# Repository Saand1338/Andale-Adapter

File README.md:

# Andale Adapter

The Andale Adapter Project is a Wii Remote–sized adapter for Wii Guitar Hero Controllers, powered by a Raspberry Pi Pico/Pico W running Santroller firmware.
This project, through the Santroller firmware, enables these controllers to function on PC/Xbox/PlayStation platforms through USB connectivity, or though Bluetooth via custom recievers also powered by a Raspberry Pi Pico W running Santroller firmware.
The circuit boards have been designed with hand assembly in mind, and requires the soldering of both through-hole components and surface mount devices (SMD). The use of SMD components makes a soldering plate recommended equipment, but sufficient pad clearence has been used to enable careful hand soldering.

---

## Repository Structure

This repository contains three main sections:

1. **Andale Adapter** - the Adapter itself, the "brains" of the project.
2. **Slim Receiver** - a compact Bluetooth receiver, designed for low height.
3. **Tiny Receiver** - a minimal volume Bluetooth receiver, designed for portability.

All three sections include:
- KiCAD project files and Gerber outputs.
- STL files for 3D printed enclosures.
- Autodesk Fusion project files for the STLs.
- Bills of Material (BOM) files in CSV format.

> **Note:** All enclosure STLs are designed for resin printing. Extensive use of overhangs makes them less ideal for FDM printing.

---

## Overview

The Andale Adapter is designed with certain optional elements. Depending on the desired configuration, builders can choose to integrate multiple additional features:

 Feature | Description |
----------|--------------|
 Bluetooth and/or USB connectivity | Supports both wireless and wired operation. |
 RGB LED support | Allows support for up to 10 RGB LEDs on customised PCBs though a USB Micro port. |
 Controller authentication support | Required for consoles that need controller verification, done so over a regular USB port. |
 AA battery power | Recommended for Bluetooth operation. Designed around NiMH rechargable batteries. |

> **Note:** For a Bluetooth setup USB Auth is not required on the adapter. It's only required for wired configuration on console systems that require it.

---

## Assembly Order

Due to the mixed component types and modular structure, the following rough build order is recommended:

1. Prepare customised components (e.g., modified headers, trimmed USB connectors).
2. Solder Surface Mount Devices (SMDs).
3. Solder USB connectors (if applicable).
4. Solder through-hole components (e.g., headers, battery terminals).
5. Solder add-in boards (Pico, Nunchuck adapter, accelerometer).
6. Final assembly into enclosures.

---

## Andale Adapter

The Andale Adapter is the primary focus of the project, and contains the most complex components.
A small internal cable can be made to route the Pico USB Micro to a USB-C breakout board, and a sample wiring diagram is included.
Due to height & space limitations, the PCBs in the adapter are 1mm thick by design.

### Adapter Components

| Component | Purpose |
|------------|----------|
| Mainboard | Core PCB carrying the Pico, accelerometer, and Nunchuck adapter. |
| Battery Board | Optional PCB for AA NiMH battery power and On/Off switch. |
| Connector Board | Optional PCB for controller authentication, RGB integration (with voltage boost). |
| Internal Cable | Adapting and routing the Pico USB Micro Port to a USB-C Port on the top of the case |

### Build Notes
- For Bluetooth setups, a Raspberry Pi Pico W is a requirement.
- For USB setups, either Pico or Pico W may be used.
- A USB cable or the USB-C breakout may be hardwired to the mainboard if preferred over using an internal USB Micro cable.

---

### Bill of Materials - Mainboard

| Part | Component Type | Part Code | Qty | Purpose | Notes |
|------|----------------|------------|------|----------|-------|
| Pi Pico W | Commercial Product | - | 1 | Controller logic | Use Pico for wired-only builds. |
| 1x10 Low Profile Male Header | Through-hole | - | 2 | Mount for Pico W | - |
| 1x05 Male Header | Through-hole | - | 1 | Mount for Nunchuck Adapter | Requires double insulator height. |
| Adafruit Nunchuck Adapter | Commercial Product | - | 1 | Nunchuck connector integration | - |
| 1x08 Low Profile Male Header | Through-hole | - | 1 | Mount for ADXL345 | - |
| Triple Axis SEN0032 ADXL345 Board | Commercial Product | - | 1 | Accelerometer | Other ADXL345 board compatibility is uncertain. |
| 1x02 Low Profile Female Header | Through-hole | - | 1 | Powerboard plug | - |
| 1x04 Low Profile Female Header | Through-hole | - | 2 | Connector board plug | Insulator height 4 or 7 mm. |
| 20V 1A Schottky Diode | SMD (SOT-123F) | MBR120VLSFT1G | 1 | Power direction regulator | Required for battery or hardwired power. |
| LED | SMD (1208) | QBLP653-S5 | 1 | Low-voltage indicator | - |
| 1.25 V Voltage Shunt | SMD (DBZ) | TLV431DBZ | 1 | Voltage detection | Must use TL**V**431 variant. |
| 3.57 kΩ Resistor | SMD (0805) | RQ73C2A3K57BTD | 1 | Voltage divider | - |
| 2.74 kΩ Resistor | SMD (0805) | RQ73C2A2K74BTD | 1 | Voltage divider | - |
| 221 Ω Resistor | SMD (0805) | RQ73C2A221RBTD | 1 | LED current limiter | Value not optimal but functional. |
| USB Male to Micro Adapter | Commercial Product | - | 1 | Internal cable | Optional; unnecessary for a directly hardwired setup. |
| Adafruit USB-C Downstream Breakout | Commercial Product | - | 1 | External connector | - |
| Silicone Ribbon Cable (4× 28 AWG) | Commercial Product | - | 1 | Internal wiring | - |

---

### Bill of Materials - Battery Board

| Part | Component Type | Part Code | Qty | Purpose | Notes |
|------|----------------|------------|------|----------|-------|
| 1x2 Male Header | Through-hole | - | 1 | Plug to mainboard | Mount upside down if using 7 mm tall header sockets. |
| On-Off Switch | Through-hole | AS11AH | 1 | Power control | - |
| AA Battery Terminal, Plate | Through-hole | Keystone 595 | 2 | Battery contact | - |
| AA Battery Terminal, Coil | Through-hole | Keystone 628 | 2 | Battery contact | - |

---

### Bill of Materials - Connector Board

| Part | Component Type | Part Code | Qty | Purpose | Notes |
|------|----------------|------------|------|----------|-------|
| 1x04 Male Header | Through-hole | - | 2 | Plug to mainboard | Mount upside down if using 7 mm tall header sockets. |
| 1x04 Low Profile Male Header | Through-hole | - | 1 | Mount for TinyBoost | - |
| USB Micro Female | Through-hole | Amphenol 10118194-0001LF | 1 | RGB integration | Nonstandard use of USB port. |
| USB A Female | Through-hole | GCT USB1046 | 1 | Controller auth | Required for wired console use. |
| Adafruit MiniBoost 5V | Commercial Product | - | 1 | Voltage boost for RGB | Skip for non-battery builds. |

---

## Slim Receiver

The Slim Receiver is a Bluetooth receiver designed for consoles or PCs.
It uses a Pico W, connects directly via USB-A, and includes a secondary port for controller auth.

### Key Characteristics
- Compact vertical height.
- Left- or right-offset USB configuration so two recievers can be used side-by-side

### Bill of Materials - Slim Receiver

| Part | Component Type | Part Code | Qty | Purpose | Notes |
|------|----------------|------------|------|----------|-------|
| Pi Pico W | Commercial Product | - | 1 | Logic | Required. |
| 1x10 Low Profile Male Header | Through-hole | - | 2 | Mount for Pico W | - |
| USB A Male | Through-hole | CNCTech 1001-011-01101 | 1 | Plug for console/PC | Offset configuration possible. |
| USB A Female | Through-hole | GCT USB1046 | 1 | Auth plug | Required for consoles needing authentication. |
| 3.18 mm → 1.78 mm Pogo Pin | Through-hole | 0926-1-15-20-75-14-11-0 | 2 | Pico testpoint connection | 2.54 mm target height. |

---

## Tiny Receiver

The Tiny Receiver alternatively offers a minimal design for ease of transport. It does however have a larger vertical height and worse horizontal clearance, so fitting multiple in side-by-side USB ports may be impossible.
It mounts the Pico W directly underneath the PCB, requiring precise soldering and a fine-tipped soldering iron.

### Build Notes
- Mount the Pico W on the underside and solder through the seven marked pads.
- Trim USB plug and port wings to fit enclosure.
- Difficult to build & repair. Not recommended.

### Bill of Materials - Tiny Receiver

| Part | Component Type | Part Code | Qty | Purpose | Notes |
|------|----------------|------------|------|----------|-------|
| Pi Pico W | Commercial Product | - | 1 | Logic | Mounted underside. |
| USB A Male | Through-hole | CNCTech 1001-011-01101 | 1 | Main plug | Trim wings to < 1 mm. |
| USB A Female | Through-hole | GCT USB1046 | 1 | Auth port | Trim wings to < 1 mm. |

---

## Hardware Fasteners

A bulk pack of metric M2 machine screws is recommended.

| Section | Part | Component Type | Qty | Purpose |
|----------|------|----------------|------|----------|
| Adapter Shell | M2 Machine Screw 4 mm | Commercial Product | 3 | Mounts mainboard, power board |
| Adapter Shell | M2 Machine Screw 6 mm | Commercial Product | 4 | Mounts breakout, shell rear |
| Adapter Shell | M2 Machine Screw 8 mm | Commercial Product | 2 | Mounts shell front |
| Slim Shell | M2 Machine Screw 6 mm | Commercial Product | 4 | Holds halves together |
| Tiny Shell | M2 Machine Screw 6 mm | Commercial Product | 4 | Holds halves together |

---

## Firmware

This project uses Santroller firmware by sanjay900.
All credit for firmware functionality belongs to the original author.

For more information visit the Santroller website.

---

## Thanks

Thank you to Sanjay & the Santroller community. They were openly welcoming and provided a great deal of support and validation during the development of this project. It would not have been possible without them.

---

## Licensing

All designs, documents, and files in this repository are released under the **Creative Commons Attribution–ShareAlike (CC-BY-SA)** license.
You are free to modify, distribute, and remix, provided that proper credit is given and derivatives are shared under the same terms.

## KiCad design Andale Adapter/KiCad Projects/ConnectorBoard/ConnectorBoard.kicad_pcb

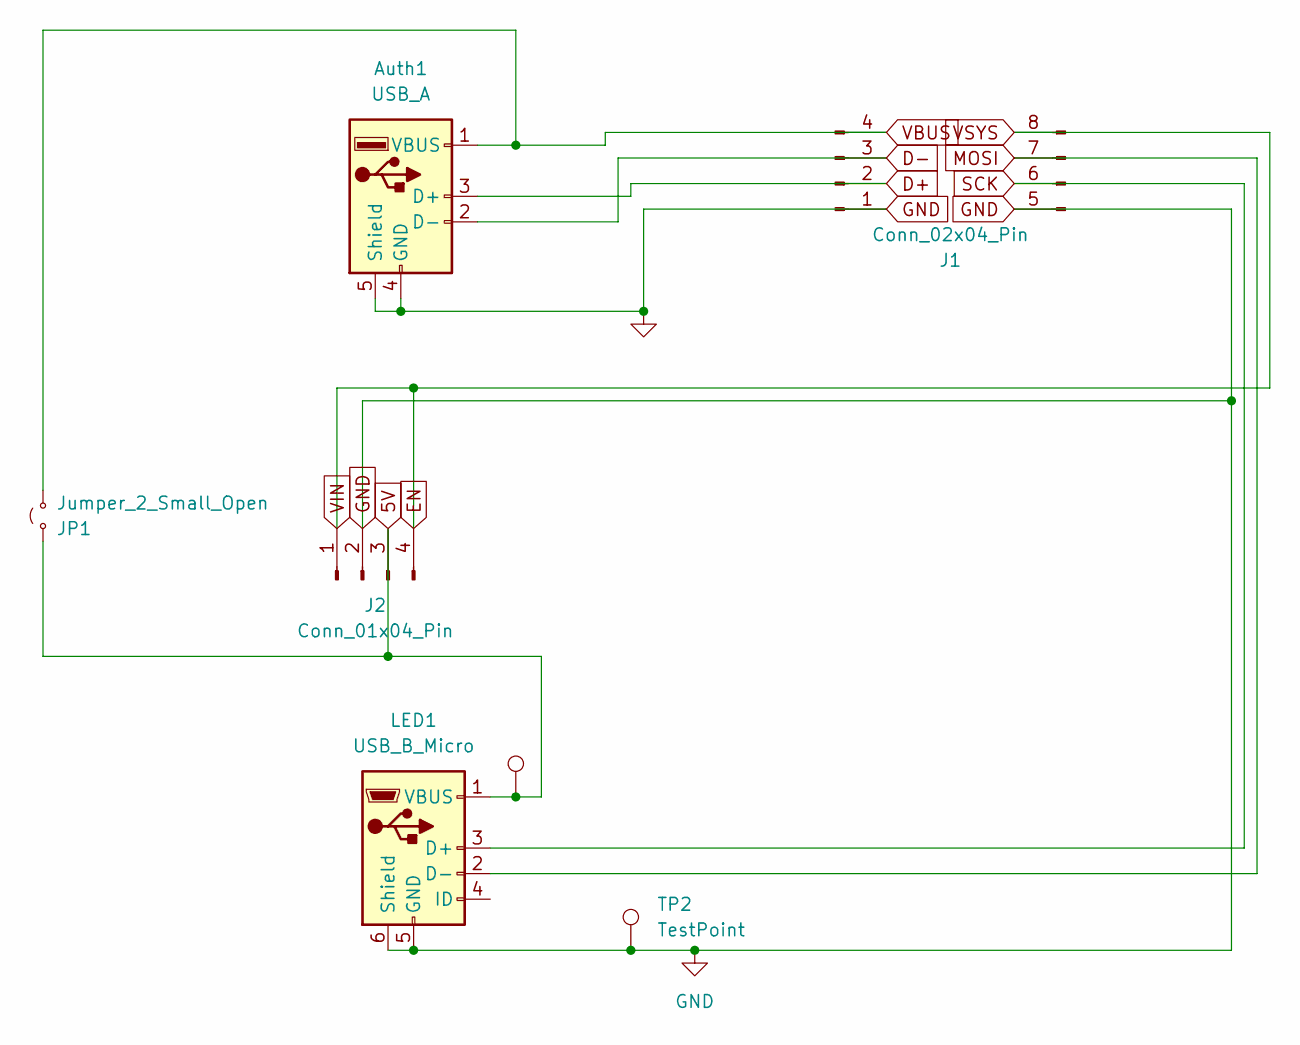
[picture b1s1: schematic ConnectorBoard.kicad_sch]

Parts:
Auth1: USB_A; USB_A_Receptacle_GCT_USB1046_Model
J1: Conn_02x04_Pin; PinHeader_2x04_P2.54mm_Vertical_Inverted
J2: Conn_01x04_Pin; PinHeader_1x04_P2.54mm_Vertical
JP1: Jumper_2_Small_Open; SolderJumper-2_P1.3mm_Open_TrianglePad1.0x1.5mm
LED1: USB_B_Micro; USB_Micro-B_Amphenol_10118194-0001LF_Horizontal_Model
TP1, TP2: TestPoint; TestPoint_Pad_D1.5mm

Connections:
5V: J2.3, JP1.2 (B), LED1.1 (VBUS), TP1.1
D+: Auth1.3 (D+), J1.2
D-: Auth1.2 (D-), J1.3
EN: J1.8, J2.1, J2.4
GND: Auth1.4 (GND), Auth1.5 (Shield), J1.1, J1.5, J2.2, LED1.5 (GND), LED1.6 (Shield), TP2.1
MOSI: J1.7, LED1.2 (D-)
SCK: J1.6, LED1.3 (D+)
VBUS: Auth1.1 (VBUS), J1.4, JP1.1 (A)

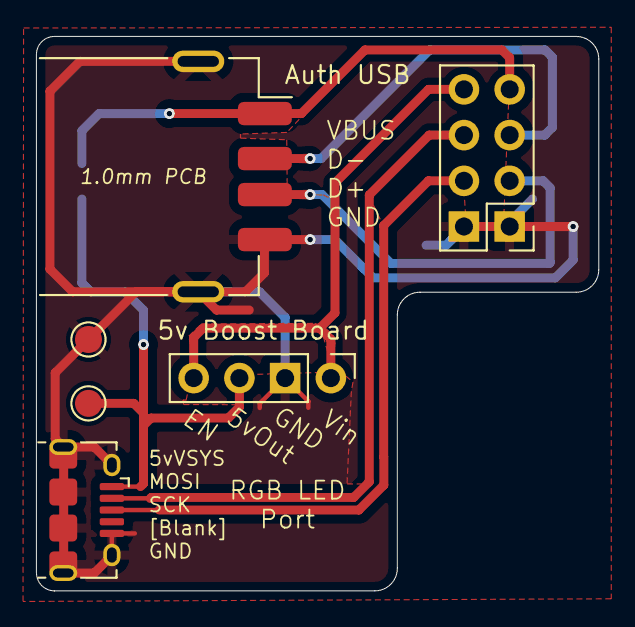
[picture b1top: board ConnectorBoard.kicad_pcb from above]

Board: 2 copper layers, 31.2 x 30.8 mm, 7 parts (1 on the bottom side), 8 nets.

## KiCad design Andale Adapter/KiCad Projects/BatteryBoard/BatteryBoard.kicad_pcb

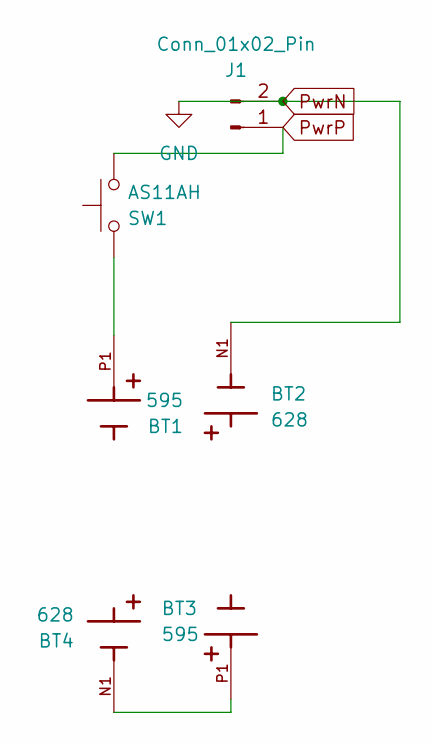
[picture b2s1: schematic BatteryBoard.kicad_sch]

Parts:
BT1: 595; BAT_595; PARTREV E
BT2, BT4: 628; BAT_628; PARTREV A
BT3: 595; BAT_595_NoBatt; PARTREV E
J1: Conn_01x02_Pin; PinHeader_1x02_P2.54mm_Vertical-Inverted
SW1: AS11AH

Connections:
unnamed: BT1.P1, SW1.2
unnamed: BT3.P1, BT4.N1
PwrN: BT2.N1, J1.2
PwrP: J1.1, SW1.1

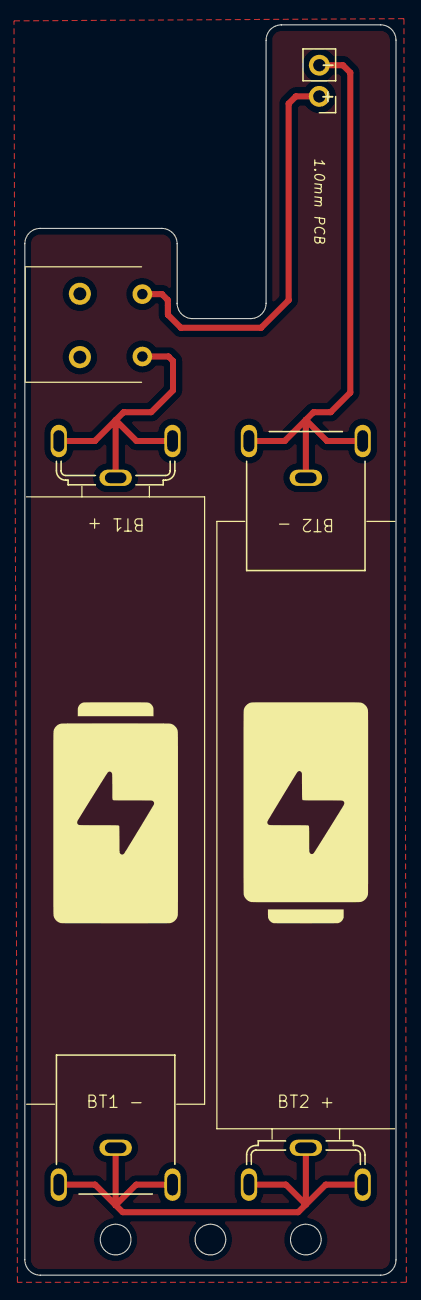
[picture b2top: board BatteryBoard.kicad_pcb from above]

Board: 2 copper layers, 30.2 x 101.9 mm, 6 parts (0 on the bottom side), 4 nets.

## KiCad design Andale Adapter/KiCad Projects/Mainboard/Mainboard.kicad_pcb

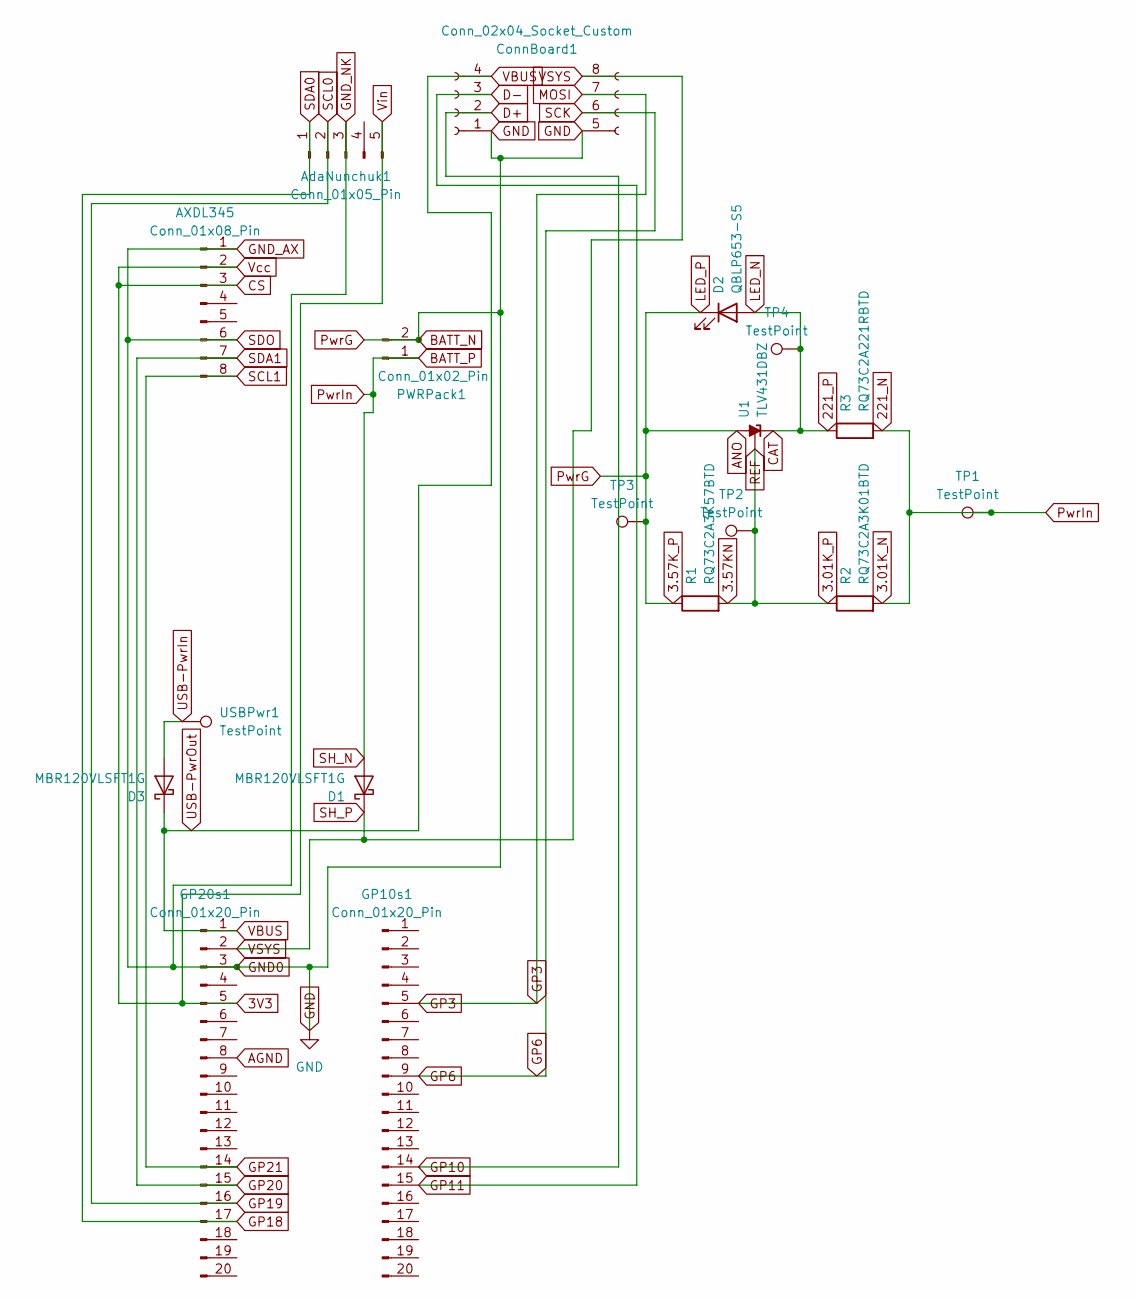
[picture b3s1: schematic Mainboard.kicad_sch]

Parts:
AXDL345: Conn_01x08_Pin; PinHeader_1x08_P2.54mm_Vertical-LowProfile
AdaNunchuk1: Conn_01x05_Pin; PinHeader_1x05_P2.54mm_Vertical-DoubleInsulator
ConnBoard1: Conn_02x04_Socket_Custom; PinSocket_2x04_P2.54mm_Vertical-4mm_Mirrored
D1, D3: MBR120VLSFT1G; D_SOD-123F-HandSoldering-0.25mm
D2: QBLP653-S5; LED_1208_Metric_Pad2.4x3.20mm_HandSolder
GP10s1, GP20s1: Conn_01x20_Pin; PinHeader_1x20_P2.54mm_Vertical-LowProfile
PWRPack1: Conn_01x02_Pin; PinSocket_1x02_P2.54mm_Vertical-4mm
R1: RQ73C2A3K57BTD; R_0805_2012Metric_Pad1.20x1.40mm_HandSolder
R2: RQ73C2A3K01BTD; R_0805_2012Metric_Pad1.20x1.40mm_HandSolder
R3: RQ73C2A221RBTD; R_0805_2012Metric_Pad1.20x1.40mm_HandSolder
TP1, TP2, TP3, TP4: TestPoint; TestPoint_Pad_D1.0mm
U1: TLV431DBZ; SOT-23-HandSoldering-0.25mm
USBPwr1: TestPoint; TestPoint_Pad_D1.5mm

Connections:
3.01K_P: R1.2, R2.1, TP2.1, U1.1 (REF)
3V3: AXDL345.2, AXDL345.3, AdaNunchuk1.5, GP20s1.5
221_N: D1.2 (A), PWRPack1.1, R2.2, R3.2, TP1.1
221_P: D2.2 (A), R3.1, TP4.1, U1.2 (K)
AGND: GP20s1.8
D+: ConnBoard1.2, GP10s1.14
D-: ConnBoard1.3, GP10s1.15
GND: AXDL345.1, AXDL345.6, AdaNunchuk1.3, ConnBoard1.1, ConnBoard1.5, D2.1 (K), GP10s1.3, GP10s1.8, GP10s1.13, GP10s1.18, GP20s1.3, GP20s1.13, GP20s1.18, PWRPack1.2, R1.1, TP3.1, U1.3 (A)
GP3: ConnBoard1.7, GP10s1.5
GP6: ConnBoard1.6, GP10s1.9
GP18: AdaNunchuk1.1, GP20s1.17
GP19: AdaNunchuk1.2, GP20s1.16
GP20: AXDL345.7, GP20s1.15
GP21: AXDL345.8, GP20s1.14
SH_P: ConnBoard1.8, D1.1 (K), GP20s1.2
USB-PwrIn: D3.2 (A), USBPwr1.1
USB-PwrOut: ConnBoard1.4, D3.1 (K), GP20s1.1

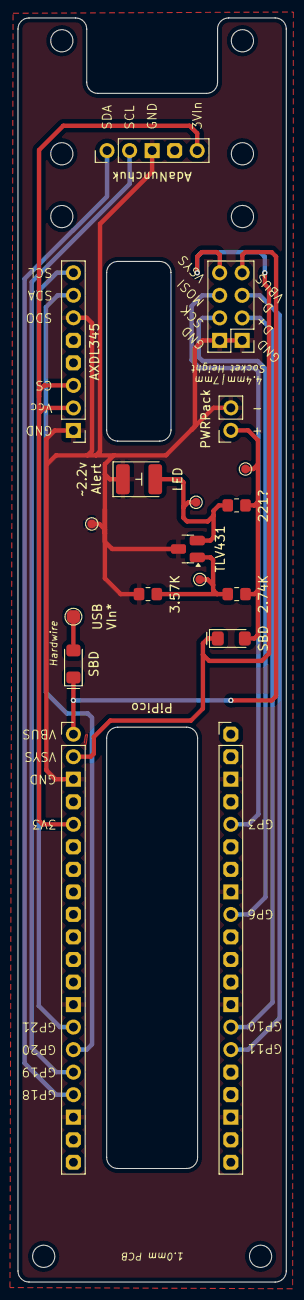
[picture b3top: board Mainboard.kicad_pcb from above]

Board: 2 copper layers, 30.2 x 142.5 mm, 18 parts (0 on the bottom side), 16 nets.

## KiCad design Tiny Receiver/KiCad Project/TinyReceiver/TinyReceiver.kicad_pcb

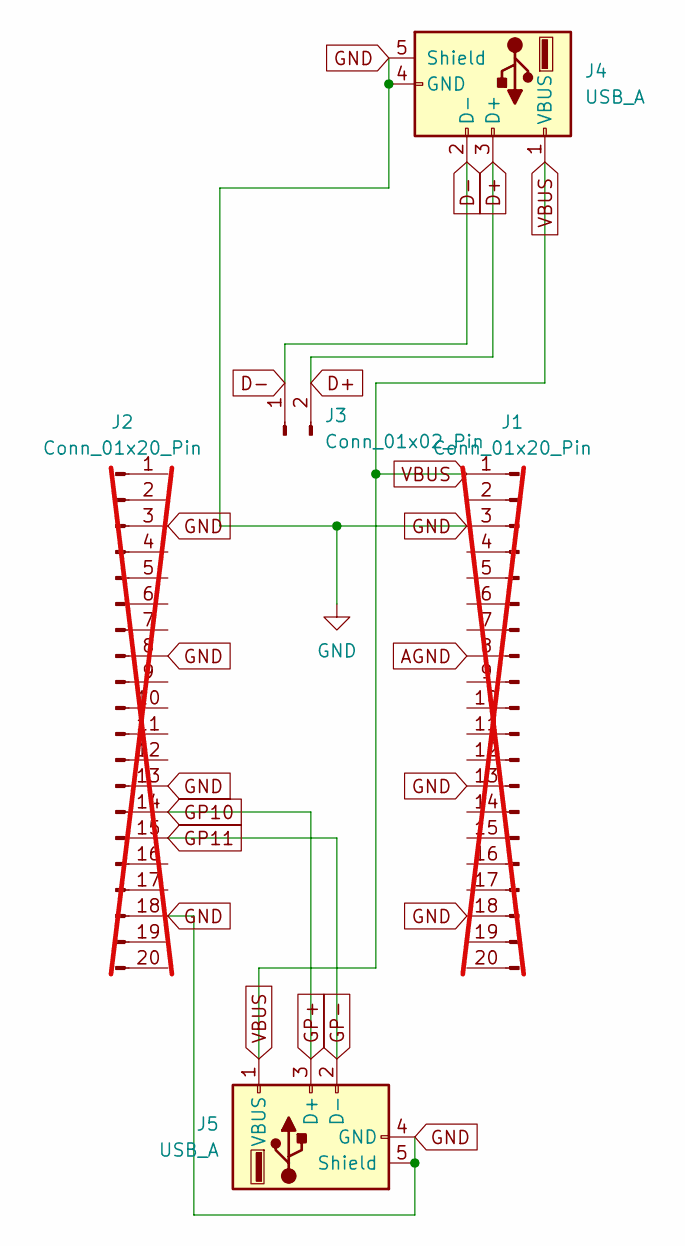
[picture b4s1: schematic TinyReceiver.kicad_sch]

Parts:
J1, J2: Conn_01x20_Pin; PinHeader_1x20_P2.54mm_Vertical_Low_Profile; not fitted
J3: Conn_01x02_Pin; PinHeader_1x02_P2.54mm_Vertical
J4: USB_A; USB_A_CNCTech_1001-011-01101_Horizontal
J5: USB_A; USB_A_Receptacle_GCT_USB1046_Model

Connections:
AGND: J1.8
D+: J3.2, J4.3 (D+)
D-: J3.1, J4.2 (D-)
GND: J1.3, J1.13, J1.18, J2.3, J2.8, J2.13, J2.18, J4.4 (GND), J4.5 (Shield), J5.4 (GND), J5.5 (Shield)
GP+: J2.14, J5.3 (D+)
GP-: J2.15, J5.2 (D-)
VBUS: J1.1, J4.1 (VBUS), J5.1 (VBUS)

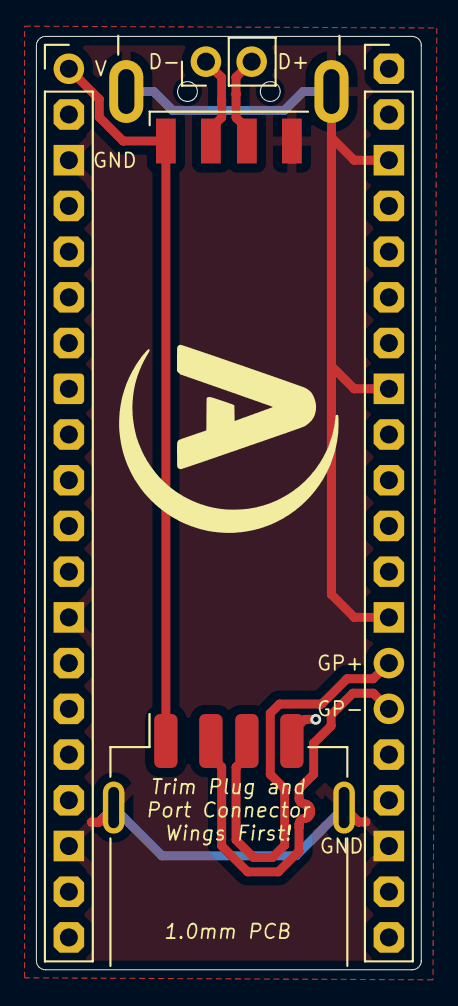
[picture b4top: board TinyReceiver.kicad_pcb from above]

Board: 2 copper layers, 21.4 x 51.8 mm, 5 parts (0 on the bottom side), 6 nets.

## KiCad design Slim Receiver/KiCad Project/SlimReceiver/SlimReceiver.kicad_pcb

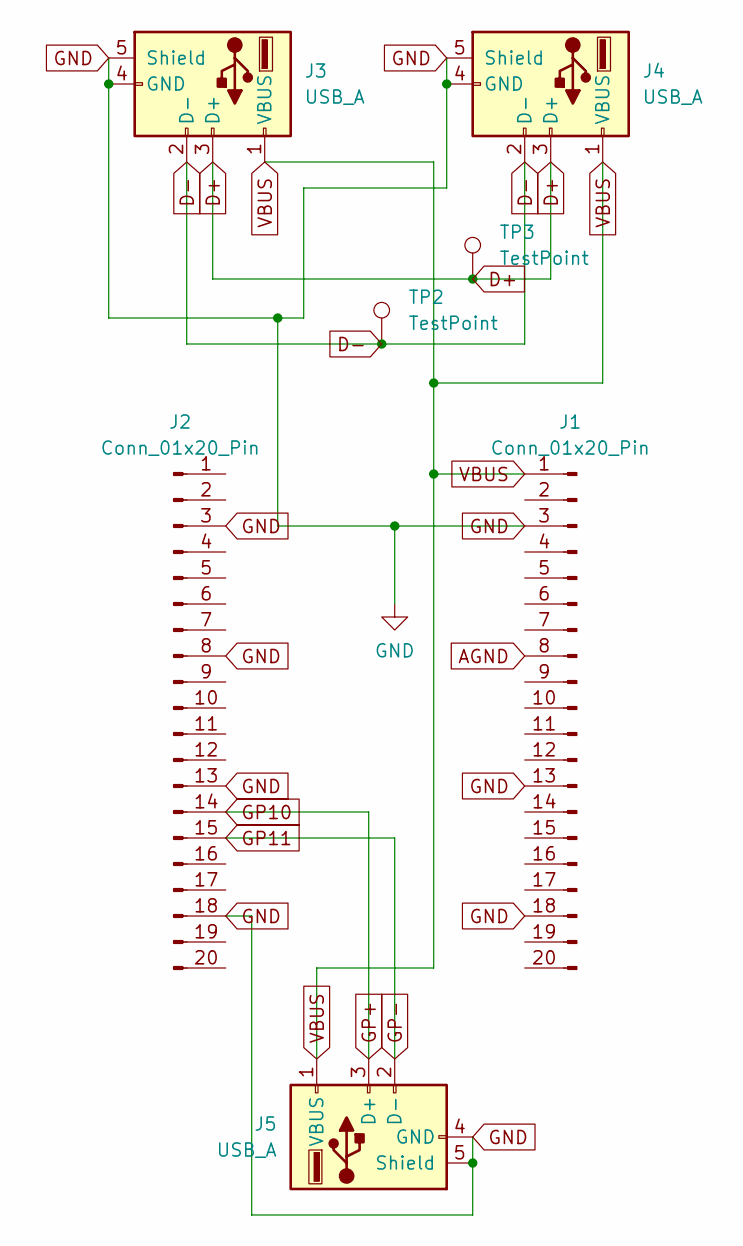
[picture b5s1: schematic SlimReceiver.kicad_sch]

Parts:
J1, J2: Conn_01x20_Pin; PinHeader_1x20_P2.54mm_Vertical_Low_Profile
J3: USB_A; USB_A_CNCTech_1001-011-01101_Horizontal_NoModel
J4: USB_A; USB_A_CNCTech_1001-011-01101_Horizontal
J5: USB_A; USB_A_Receptacle_GCT_USB1046_Model
TP2, TP3: TestPoint; MM_0926-1-15-20-75-14-11-0

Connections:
AGND: J1.8
D+: J3.3 (D+), J4.3 (D+), TP3.1
D-: J3.2 (D-), J4.2 (D-), TP2.1
GND: J1.3, J1.13, J1.18, J2.3, J2.8, J2.13, J2.18, J3.4 (GND), J3.5 (Shield), J4.4 (GND), J4.5 (Shield), J5.4 (GND), J5.5 (Shield)
GP+: J2.14, J5.3 (D+)
GP-: J2.15, J5.2 (D-)
VBUS: J1.1, J3.1 (VBUS), J4.1 (VBUS), J5.1 (VBUS)

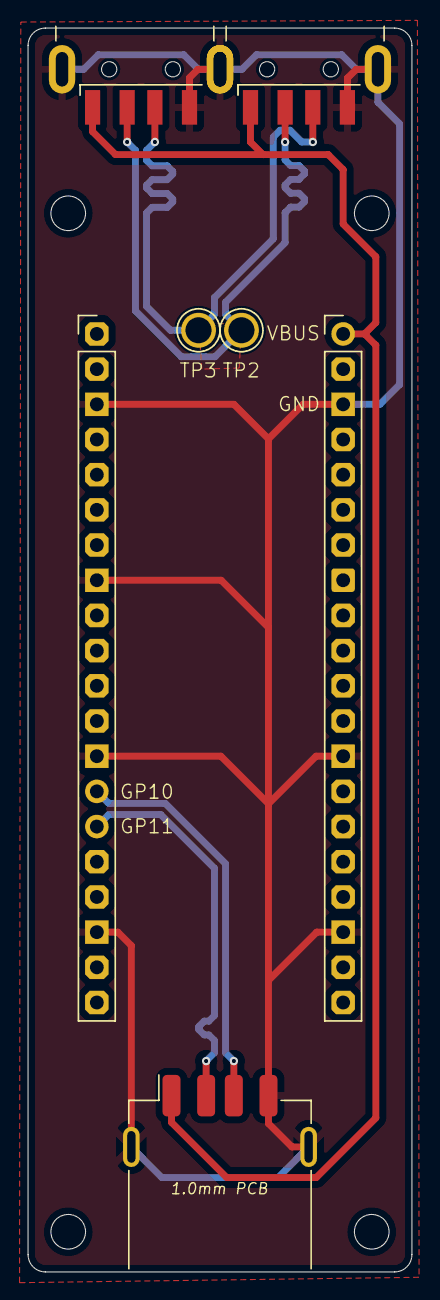
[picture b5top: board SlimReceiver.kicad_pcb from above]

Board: 2 copper layers, 27.7 x 89.8 mm, 7 parts (0 on the bottom side), 6 nets.

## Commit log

2025-10-31 Initial commit, all project files and meta files
2025-10-31 Fixed minor formatting
